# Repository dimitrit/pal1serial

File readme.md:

# PAL-1 Serial Interface Adapter

The PAL-1 Serial Interface Adapter is an expansion module for the PAL-1 system<sup>1</sup> based on the Motorola MC6850 Asynchronous Communications Interface Adapter (ACIA)<sup>2</sup>. The design was inspired by a homebrew project in CPC Schneider International magazine<sup>3</sup>.

## Acknowledgements

PAL-1 and the PAL-1 logo used with kind permission of Liu Ganning.

## References
1. Liu Ganning, ‘PAL-1 Microcomputer User Manual’, 2020 <http://pal.aibs.ws/assets/PAL_en.pdf> [accessed 21 July 2022].
2. Motorola Semiconductors, ‘MC6850, Asynchronous Communications Interface Adapter (ACIA)’ (Motorola Semiconductors, 1994).
3. Joachim Schweda, ‘Schnittstelle RS-232 im Selbstbau’, CPC Schneider International, 7.3 (1986), 88-92.

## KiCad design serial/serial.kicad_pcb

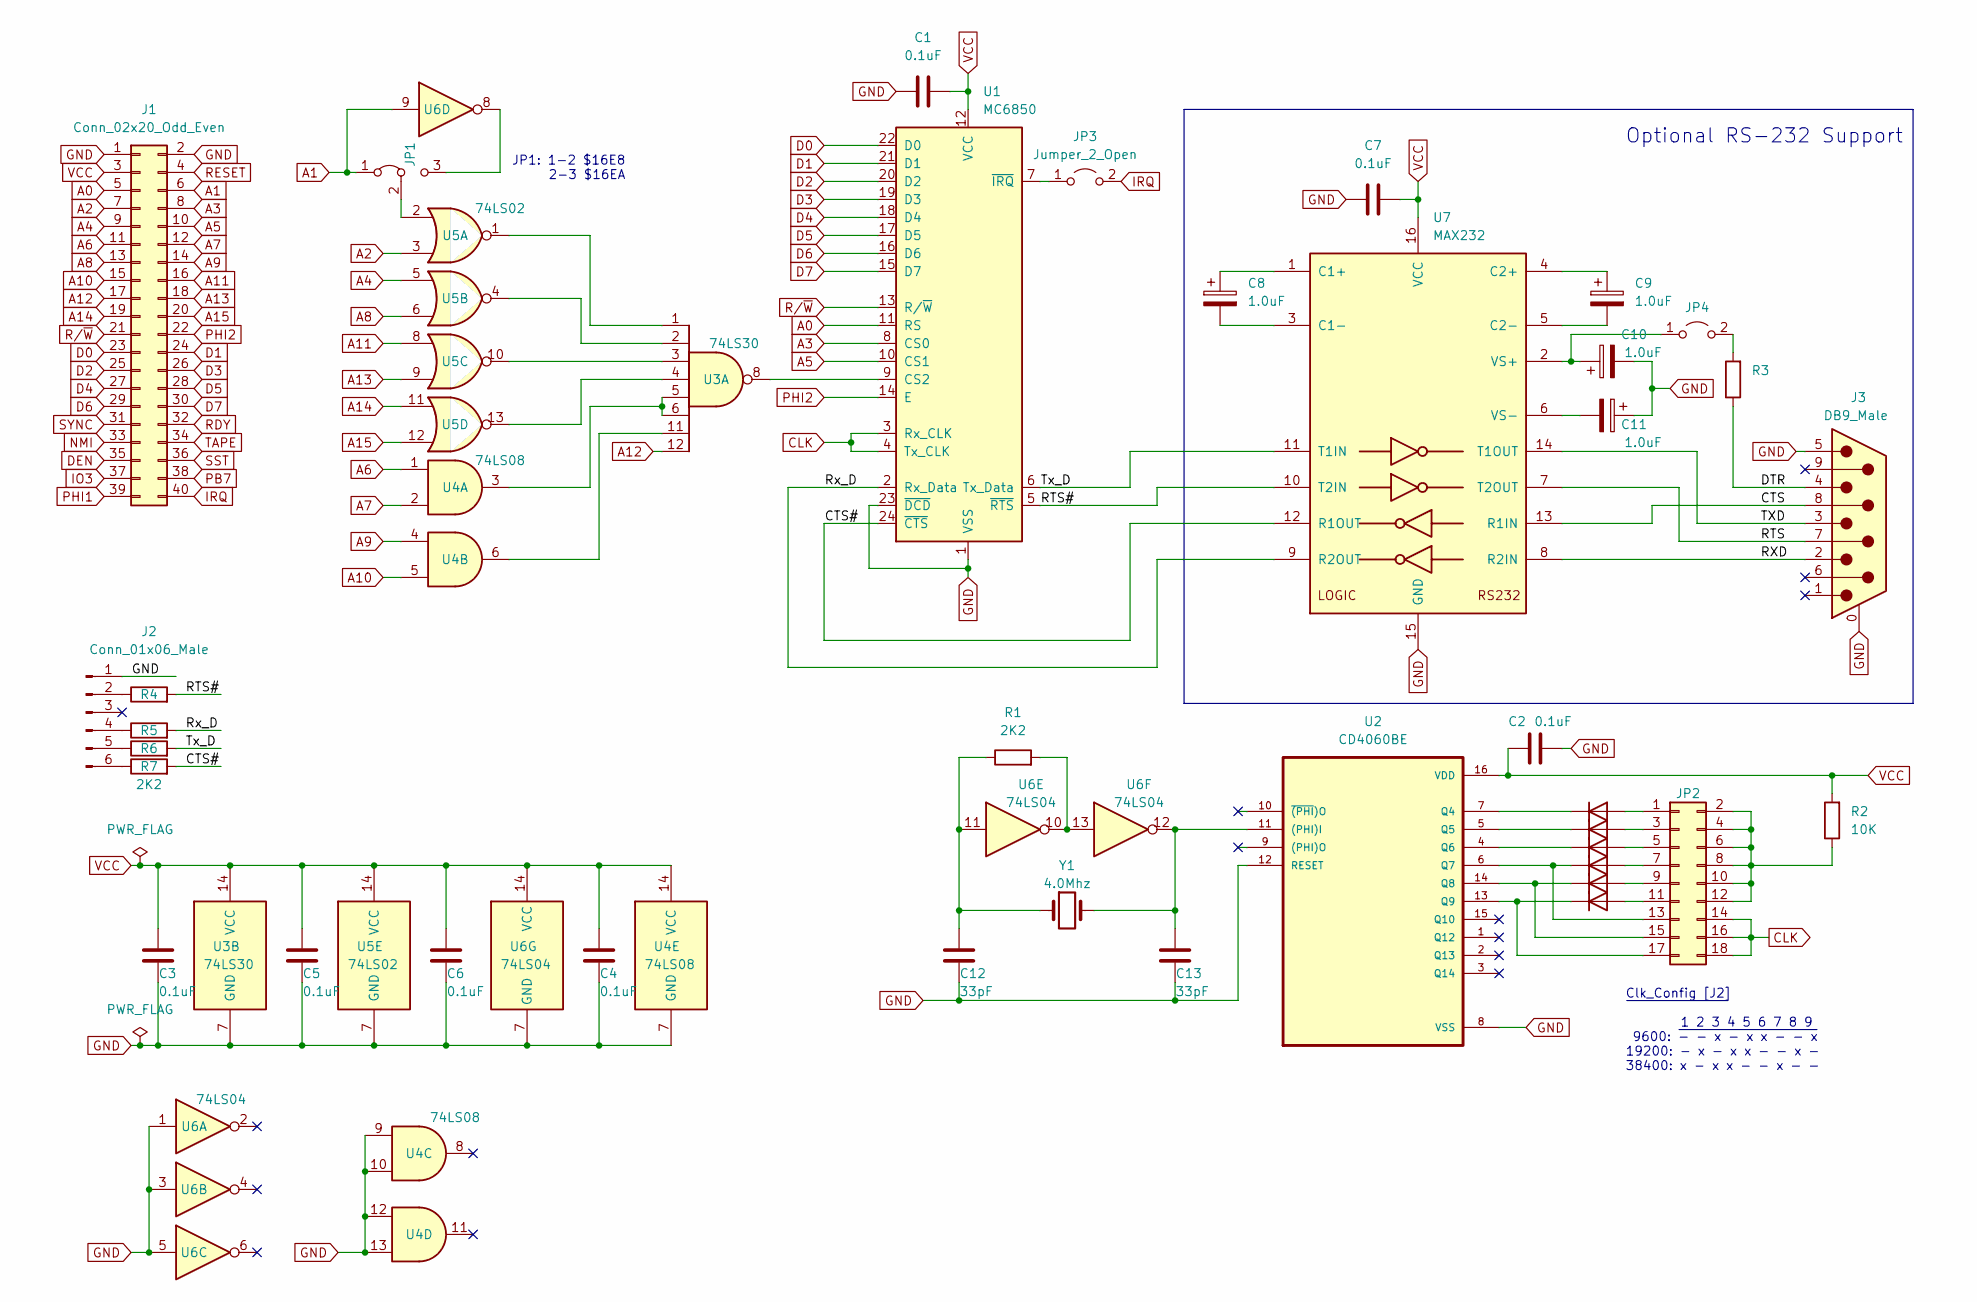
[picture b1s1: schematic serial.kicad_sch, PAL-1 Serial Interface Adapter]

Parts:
C1, C2, C3, C4, C5, C6, C7: 0.1uF; C_Disc_D3.0mm_W1.6mm_P2.50mm
C8, C9, C10, C11: 1.0uF; CP_Radial_D5.0mm_P2.50mm
C12, C13: 33pF; C_Disc_D3.0mm_W1.6mm_P2.50mm
D1, D2, D3, D4, D5, D6: 1N4148; D_DO-35_SOD27_P7.62mm_Horizontal
J1: Conn_02x20_Odd_Even; PinHeader_2x20_P2.54mm_Vertical
J2: Conn_01x06_Male; PinHeader_1x06_P2.54mm_Horizontal
J3: DB9_Male; DSUB-9_Male_Horizontal_P2.77x2.84mm_EdgePinOffset7.70mm_Hou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
JP1: addr select; PinHeader_1x03_P2.54mm_Vertical
JP2: Conn_02x09_Odd_Even; PinHeader_2x09_P2.54mm_Vertical
JP3, JP4: Jumper_2_Open; PinHeader_1x02_P2.54mm_Vertical
R1, R4, R5, R6, R7: 2K2; R_Axial_DIN0207_L6.3mm_D2.5mm_P7.62mm_Horizontal
R2: 10K; R_Axial_DIN0207_L6.3mm_D2.5mm_P7.62mm_Horizontal
R3: R_Axial_DIN0207_L6.3mm_D2.5mm_P7.62mm_Horizontal
U1: MC6850; DIP-24_W15.24mm
U2: CD4060BE; DIP-16_W7.62mm
U3: 74LS30; DIP-14_W7.62mm
U4: 74LS08
U5: 74LS02; DIP-14_W7.62mm
U6: DIP-14_W7.62mm
U7: MAX232; DIP-16_W7.62mm
Y1: 4.0Mhz; Crystal_HC49-U_Vertical

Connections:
/CTS: J3.8, U7.13 (R1IN)
/CTS#: R7.2, U1.24 (~CTS), U7.12 (R1OUT)
/DTR: J3.4, R3.1
/RTS: J3.7, U7.7 (T2OUT)
/RTS#: R4.2, U1.5 (~RTS), U7.10 (T2IN)
/RXD: J3.2, U7.8 (R2IN)
/Rx_D: R5.2, U1.2 (Rx_Data), U7.9 (R2OUT)
/TXD: J3.3, U7.14 (T1OUT)
/Tx_D: R6.2, U1.6 (Tx_Data), U7.11 (T1IN)
A0: J1.5, U1.11 (RS)
A1: J1.6, JP1.1 (A), U6.9
A2: J1.7, U5.3
A3: J1.8, U1.8 (CS0)
A4: J1.9, U5.5
A5: J1.10, U1.10 (CS1)
A6: J1.11, U4.1
A7: J1.12, U4.2
A8: J1.13, U5.6
A9: J1.14, U4.4
A10: J1.15, U4.5
A11: J1.16, U5.8
A12: J1.17, U3.12
A13: J1.18, U5.9
A14: J1.19, U5.11
A15: J1.20, U5.12
CLK: JP2.14, JP2.16, JP2.18, U1.3 (Rx_CLK), U1.4 (Tx_CLK)
D0: J1.23, U1.22 (D0)
D1: J1.24, U1.21 (D1)
D2: J1.25, U1.20 (D2)
D3: J1.26, U1.19 (D3)
D4: J1.27, U1.18 (D4)
D5: J1.28, U1.17 (D5)
D6: J1.29, U1.16 (D6)
D7: J1.30, U1.15 (D7)
DEN: J1.35
GND: C1.1, C2.1, C3.1, C4.1, C5.1, C6.1, C7.1, C10.2, C11.1, C12.1, C13.1, J1.1, J1.2, J2.1, J3.0 (PAD), J3.5, U1.1 (VSS), U1.23 (~DCD), U2.8 (VSS), U2.12 (RESET), U3.7 (GND), U4.7 (GND), U4.9, U4.10, U4.12, U4.13, U5.7 (GND), U6.1, U6.3, U6.5, U6.7 (GND), U7.15 (GND)
IO3: J1.37
IRQ: J1.40, JP3.2 (B)
NMI: J1.33
unnamed: C8.1, U7.1 (C1+)
unnamed: C8.2, U7.3 (C1-)
unnamed: C9.1, U7.4 (C2+)
unnamed: C9.2, U7.5 (C2-)
unnamed: C10.1, JP4.1 (A), U7.2 (VS+)
unnamed: C11.2, U7.6 (VS-)
unnamed: C12.2, R1.1, U6.11, Y1.1
unnamed: C13.2, U2.11 ((PHI)I), U6.12, Y1.2
unnamed: D1.1 (K), U2.7 (Q4)
unnamed: D1.2 (A), JP2.1
unnamed: D2.1 (K), U2.5 (Q5)
unnamed: D2.2 (A), JP2.3
unnamed: D3.1 (K), U2.4 (Q6)
unnamed: D3.2 (A), JP2.5
unnamed: D4.1 (K), JP2.13, U2.6 (Q7)
unnamed: D4.2 (A), JP2.7
unnamed: D5.1 (K), JP2.15, U2.14 (Q8)
unnamed: D5.2 (A), JP2.9
unnamed: D6.1 (K), JP2.17, U2.13 (Q9)
unnamed: D6.2 (A), JP2.11
unnamed: J2.2, R4.1
unnamed: J2.4, R5.1
unnamed: J2.5, R6.1
unnamed: J2.6, R7.1
unnamed: JP1.2 (C), U5.2
unnamed: JP1.3 (B), U6.8
unnamed: JP2.2, JP2.4, JP2.6, JP2.8, JP2.10, JP2.12, R2.1
unnamed: JP3.1 (A), U1.7 (~IRQ)
unnamed: JP4.2 (B), R3.2
unnamed: R1.2, U6.10, U6.13
unnamed: U1.9 (CS2), U3.8
unnamed: U3.1, U5.1
unnamed: U3.2, U5.4
unnamed: U3.3, U5.10
unnamed: U3.4, U5.13
unnamed: U3.5, U3.6, U4.3
unnamed: U3.11, U4.6
PB7: J1.38
PHI1: J1.39
PHI2: J1.22, U1.14 (E)
RDY: J1.32
RESET: J1.4
R/~W: J1.21, U1.13 (R/~W)
SST: J1.36
SYNC: J1.31
TAPE: J1.34
VCC: C1.2, C2.2, C3.2, C4.2, C5.2, C6.2, C7.2, J1.3, R2.2, U1.12 (VCC), U2.16 (VDD), U3.14 (VCC), U4.14 (VCC), U5.14 (VCC), U6.14 (VCC), U7.16 (VCC)

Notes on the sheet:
JP1: 1-2 $16E8 2-3 $16EA
Clk_Config [J2] ~{ } 1 2 3 4 5 6 7 8 9 9600: ~{- - x - x x - - x} 19200: - x - x x - - x - 38400: x - x x - - x - -
Optional RS-232 Support

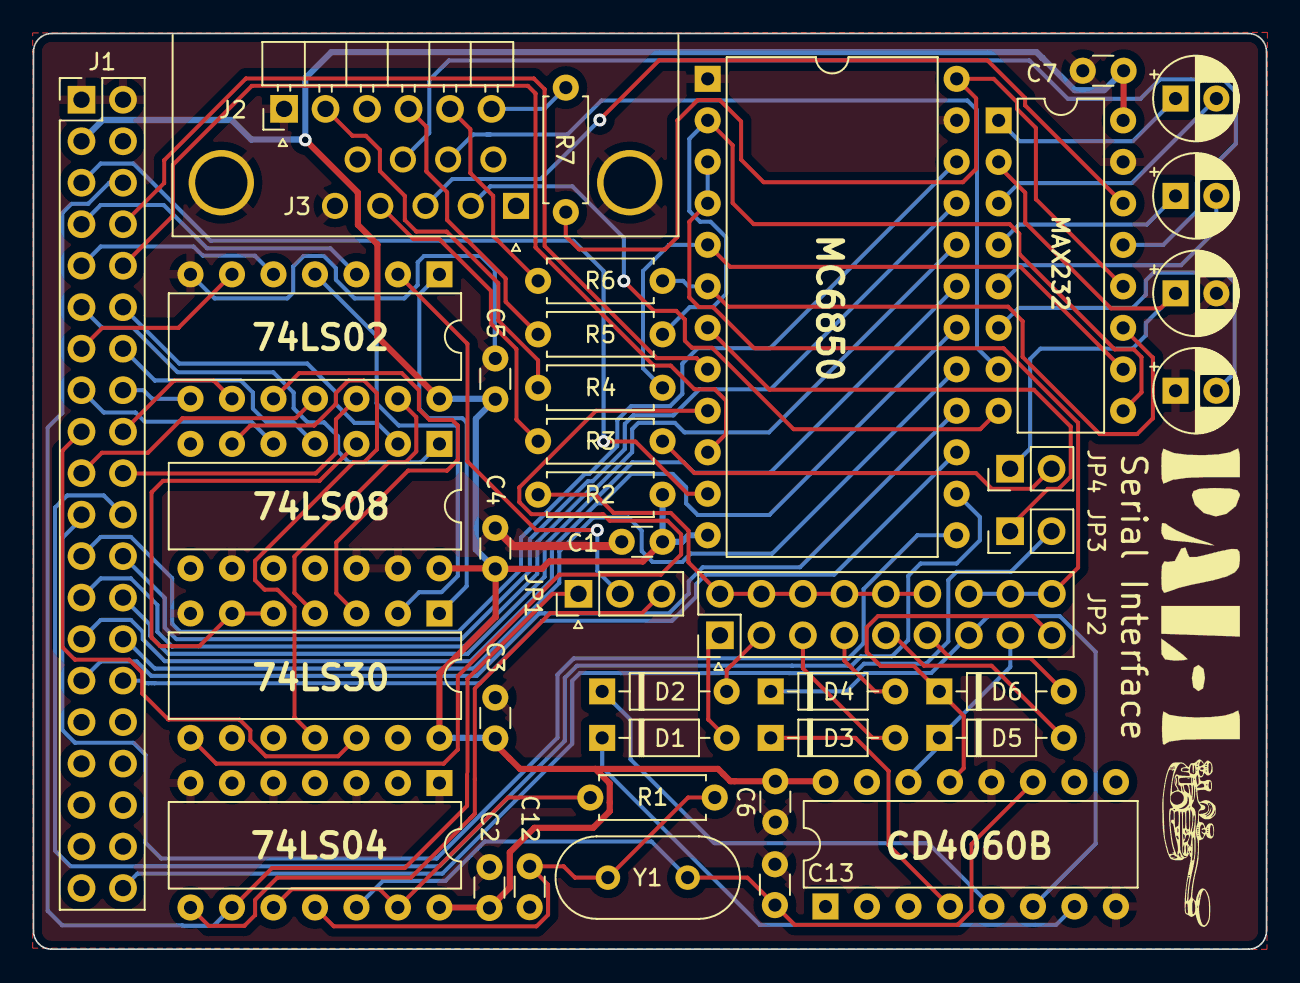
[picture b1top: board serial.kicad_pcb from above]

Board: 2 copper layers, 75.5 x 56.1 mm, 41 parts (0 on the bottom side), 76 nets.

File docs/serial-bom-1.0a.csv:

ref,qty,val,component
{C1 - C7},7,0.1uF,Unpolarized capacitor
{C8 - C11},4,1.0uF,Polarized capacitor
{C12, C13},2,33pF,Unpolarized capacitor
{D1 - D6},6,1N4148,{Standard switching diode, DO-35}
J1,1,,{Connector, double row, 2x20}
J2,1,,{Connector, single row, 1x6}
J3,1,,{Connector, 9-pin male D-SUB}
JP1,1,,{Jumper, 3-pole, pins 1+2 closed/bridged}
JP2,1,,{Connector, double row, 2x9}
{JP3, JP4},2,,{Jumper, 2-pole, open}
{R1, R4-R7},5,2K2,Resistor
R2,1,10K,Resistor
R3,1,2K7,Resistor
U1,1,MC6850,Asynchronous Communications Interface Adapter 1MHz
U2,1,CD4060BE,{14-stage binary counter/divider}
U3,1,74LS30,8-input NAND gate
U4,1,74LS08,{Quad 2-input AND gate}
U5,1,74LS02,{Quad 2-input NOR gate}
U6,1,74LS04,Hex Inverter
U7,1,MAX232,{Dual RS232 driver/receiver}
Y1,1,4.0Mhz,Two pin crystal

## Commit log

2022-10-11 Add 3rd party docs
2022-10-13 Add draft schema
2022-10-13 Add documentation
2022-10-14 Add TTL header
2022-10-21 Minor improvements
2022-10-21 Update figures
2022-10-21 Add Bill of Materials
2022-10-23 Rename images
2022-10-24 Add serial adapter block diagram
2022-10-28 Add BASIC example
2022-10-31 Update schematic
2022-10-31 Add schematic diagram
2022-11-01 Fix typo
2022-11-05 Update schematic to enable 9.6-38.4kHz clock
2022-11-05 Add assembler example
2022-11-06 Update Serial Interface block diagram
2022-11-12 Update images
2022-11-12 Route pcb
2022-11-12 Routing improvements
2022-11-13 Update BOM
2022-11-14 Update BASIC example
2022-11-14 Remove outdated pdf
2022-11-15 Remove redundant files
2022-11-16 Ignore build artifacts
2022-11-16 Rename asm example
2022-11-16 Minor change to block diagram
2022-11-19 Sent for manufacturing
2022-11-19 Move DB-9 serial connector fraction closer to PCB edge
2022-12-20 Update TEST.BAS
    Fix typos
2022-12-22 Minor improvements to RS232 Driver/Receiver section
2023-10-21 Update documentation
2023-10-21 Update design
